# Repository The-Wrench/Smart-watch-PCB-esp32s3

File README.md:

# Smart-watch-PCB-esp32s3

This Project was made to show of my Electronic and IT skills.

### Content list

1. a
2. b
3. c

###

## The Story behind the Project

The Story behind the Project is relatively simple. I was Scrolling through Pinterest and looking at some DIY Smartwatches.
Pinterest then suggested to me a Hackaday article about Retro LED Segment-displays/Matrix-displays, in which i immeadetly found interest.
One of the listed Displays did catch my Eye, the HDSP-2000 Series Alphanumeric Matrix Display in DIP-Package format made by HP.
In that moment i knew i needed one of these Chips just to play around, perhaps even use in an actual Project; This is that Project.
So i Started to Design my ESP32s3 based smartwatch which would use the HDSP-2000 as the Display.

## Goals for this Project:

- [x]  Design a RTC/c Circuit
- [x]  Design the HDSP-2000 Driver Circuit
- [x]  Add a Buzzer
- [x]  Add an IO expander
- [x]  Add Testpads
- [ ]  SMD Solder the PCB
- [ ]  Test the PCB ==without== the Displays to verify the Driver Circuit
- [ ]  Test the PCB ==with== the Displays
- [ ]  SUCCESS! 🎉

## Quick start guide

1. Order the PCB from JLCPCB or PCBWAY (not sponsored)
2. Solder the componenets onto the board (i recommend the [SAND TECHNIQUE](https://youtu.be/DYrucIWig24?si=pEKrY5gaIevp7irn&t=319))
3. Test the PCB for connection errors or Shorts
4. insert your favorite colored HDSP-2000 series display (or other [Compatible models]())
5. Flash the Firmware [download here]().
6. Download the App [from here]().
7. SUCCESS! 🎉

## The License

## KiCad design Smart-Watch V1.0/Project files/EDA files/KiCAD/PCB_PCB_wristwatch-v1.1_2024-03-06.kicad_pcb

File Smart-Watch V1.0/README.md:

# Smartwatch-ESP32s3

## Order files

  Here you will find all Files necessary to Order the PCB from your PCB-Manufacturer of choice.
  i do recommend using either JLCPCB or PCBWAY due to the cost effectiveness and the relatively easy ordering process
  i will also provide instructions as to how to order from them. (with pictures)

## Pictures

  Here you will find Pictures documenting my Progress as well as some other Pictures.

##  Project Files

  here you will find all necassary Files to edit the PCB and Schematics.
  i also included various converted version of the schematic and PCB for use in other CAD software.

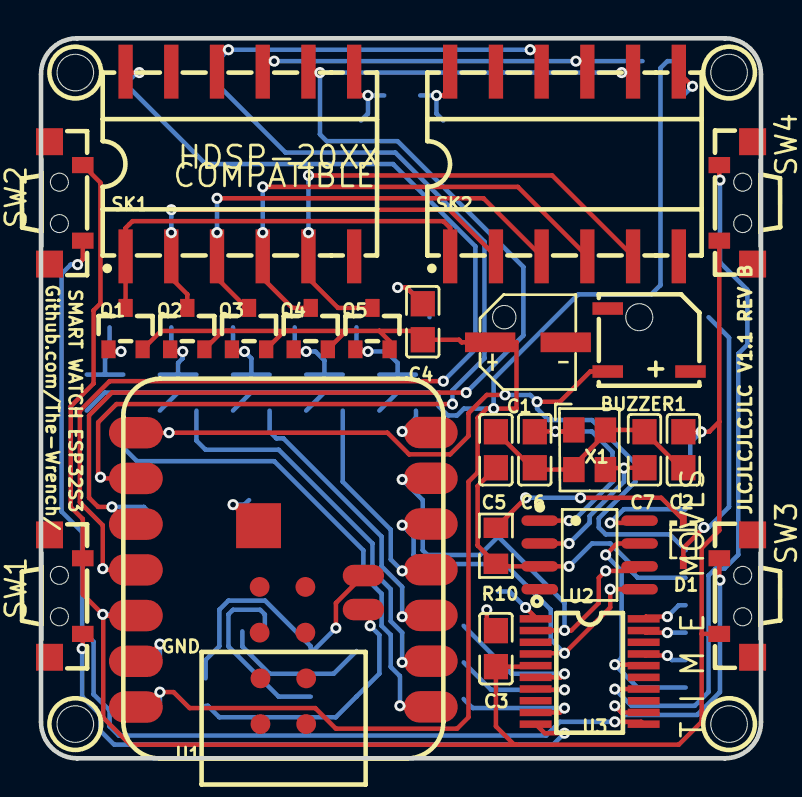
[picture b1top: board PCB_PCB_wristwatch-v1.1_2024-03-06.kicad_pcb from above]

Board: 2 copper layers, 40.0 x 40.0 mm, 70 parts (0 on the bottom side), 51 nets.

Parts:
3V3, 5V: TESTPAD
B2: UART_RX/TX_Poka-yoke; UART_RX/TX_POKAYOKE
BAT+: TESTPAD
BAT-: TESTPAD
BT1: BS-12-B3AA009; BAT-SMD_BS-12-B3AA011
BUZ: TESTPAD
BUZZER1: 4000Hz; BUZ-SMD_L5.0-W5.5-P4.60
C1: 10uF; CAP-SMD_BD5.0-L5.3-W5.3-FD
C2, C3, C4, C5: 100nF; C0805
C6: 10pF; C0805
C7: 8.2pF; C0805
D1: PMEG6002EJ,115; SOD-323F_L2.0-W1.6-LS2.5-RD
D2, D3, D4, D5, D6: 1SMAF4733A; SMAF_L3.5-W2.6-LS4.7-RD
DI2: TESTPAD
DO1, DO2: TESTPAD
GND: TESTPAD
INTIO: TESTPAD
MFP: TESTPAD
MOSI: TESTPAD
P5, P6, P7: TESTPAD
PWM: TESTPAD
Q1, Q2, Q3, Q4, Q5: SI2337DS-T1-E3; SOT-23_L2.9-W1.3-P1.90-LS2.4-BR
R1, R2, R3, R4, R5: 470Ω; R0805
R6, R7, R9, R16, R17, R18: 0Ω; R0805
R10: 1kΩ; R0805
R11, R12, R13, R14, R15: 10kΩ; R0805
SCK: TESTPAD
SCL: TESTPAD
SDA: TESTPAD
SK1, SK2: X5621FVS-2X06-C762D1226; SMD-12_L15.2-W10.2-P2.54-LS12.3-BL
SW1, SW2, SW3, SW4: GT-TC054A-H035-L1; SW-SMD_L7.8-W3.5-P4.20-EH
THERMAL: TP; TESTPAD
U1: D-; SEEEDUINO XIAO ESP32S3
U2: MCP79412-I/SN; SOIC-8_L4.9-W3.9-P1.27-LS6.0-BL
U3: PCF8574APWR; ETSSOP20_L6.5-W4.4-P0.65-LS6.4-BL
U4: YTC-A1251-02ABW; CONN-SMD_2P-P1.25_YTC-A1251-02ABW
VBAT: TESTPAD
X1: 32.768MHz; CRYSTAL-SMD_4P-L3.2-W2.5-BL-1

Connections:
3V3: 3V3.TP, C2.2, C3.2, R9.2, SW1.2, SW2.2, SW3.2, SW4.2, U1.11, U3.5
5V: 5V.TP, C1.1, C4.2, Q1.2, Q2.2, Q3.2, Q4.2, Q5.2, R7.2, R11.1, R12.1, R13.1, R14.2, R15.1, U1.13
B2_1: B2.4, U4.2
B2_2: B2.2, U4.1
BAT+: B2.1, BAT+.TP, U1.15
BAT-: B2.3, BAT-.TP, U1.14
BUZ: BUZ.TP, BUZZER1.1, U1.7
C1: R1.1, U1.0
C2: R2.1, U1.1
C3: R3.1, U1.2
C4: R4.2, U1.3
C5: R5.1, U1.6
COL1: Q1.3, SK1.1, SK2.1
COL2: Q2.3, SK1.2, SK2.2
COL3: Q3.3, SK1.3, SK2.3
COL4: Q4.3, SK1.4, SK2.4
COL5: Q5.3, SK1.5, SK2.5
D1_1: D1.1, R10.1
D1_2: BT1.1, D1.2
DI2: DI2.TP, R6.2, SK2.12
DO1: DO1.TP, R6.1, SK1.7
DO2: DO2.TP, SK2.7
GND: BT1.2, BUZZER1.2, C1.2, C2.1, C3.1, C4.1, C5.1, C6.1, C7.1, D2.2, D3.2, D4.2, D5.2, D6.2, GND.TP, R16.1, R17.1, R18.1, SK1.11, SK2.11, U1.12, U2.4, U3.15, X1.2, X1.4
INTIO: INTIO.TP, U3.1
MFP: MFP.TP, U2.7, U3.16
MOSI: MOSI.TP, SK1.12, U1.10
P0: SW1.1, U3.10
P1: SW2.1, U3.11
P2: SW3.1, U3.12
P3: SW4.1, U3.14
P5: P5.TP, U3.17
P6: P6.TP, U3.19
P7: P7.TP, U3.20
PWM: PWM.TP, SK1.8, SK2.8, U1.9
R1_2: D2.1, Q1.1, R1.2, R11.2
R2_2: D3.1, Q2.1, R2.2, R12.2
R3_2: D4.1, Q3.1, R3.2, R13.2
R4_1: D5.1, Q4.1, R4.1, R14.1
R5_2: D6.1, Q5.1, R5.2, R15.2
SCK: SCK.TP, SK1.10, SK2.10, U1.8
SCL: SCL.TP, U1.5, U2.6, U3.2
SDA: SDA.TP, U1.4, U2.5, U3.4
SK1_9: R7.1, SK1.9, SK2.9
U1_24: THERMAL.TP, U1.24
U2_1: C6.2, U2.1, X1.1
U2_2: C7.2, U2.2, X1.3
U2_8: R9.1, U2.8
U3_6: R16.2, U3.6
U3_7: R17.2, U3.7
U3_9: R18.2, U3.9
VBAT: C5.2, R10.2, U2.3, VBAT.TP

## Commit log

2024-01-28 Update README.md
    a
2024-01-28 the stuff
    adding most files necessary for pcb ordering
2024-01-28 Update README.md
    b
2024-01-29 pictures and bom
    pictures and bom
2024-02-01 a
    a
2024-02-09 adjusted design for tolerance
    adjusted the design for placement of hdsp-2000 and general small improvements
2024-02-25 changed file structure and included v1.1
    added v1.1
    changed file structure
2024-02-25 more changes to structure
    more changes to structure
2024-03-06 1.0 "release"
    basicly the 1.0 release but due to me not having built it yet its nor really the finished release
2024-03-06 1.0 "release"
    markdown fix
2024-03-09 added pcb render pictures
    pcb render
